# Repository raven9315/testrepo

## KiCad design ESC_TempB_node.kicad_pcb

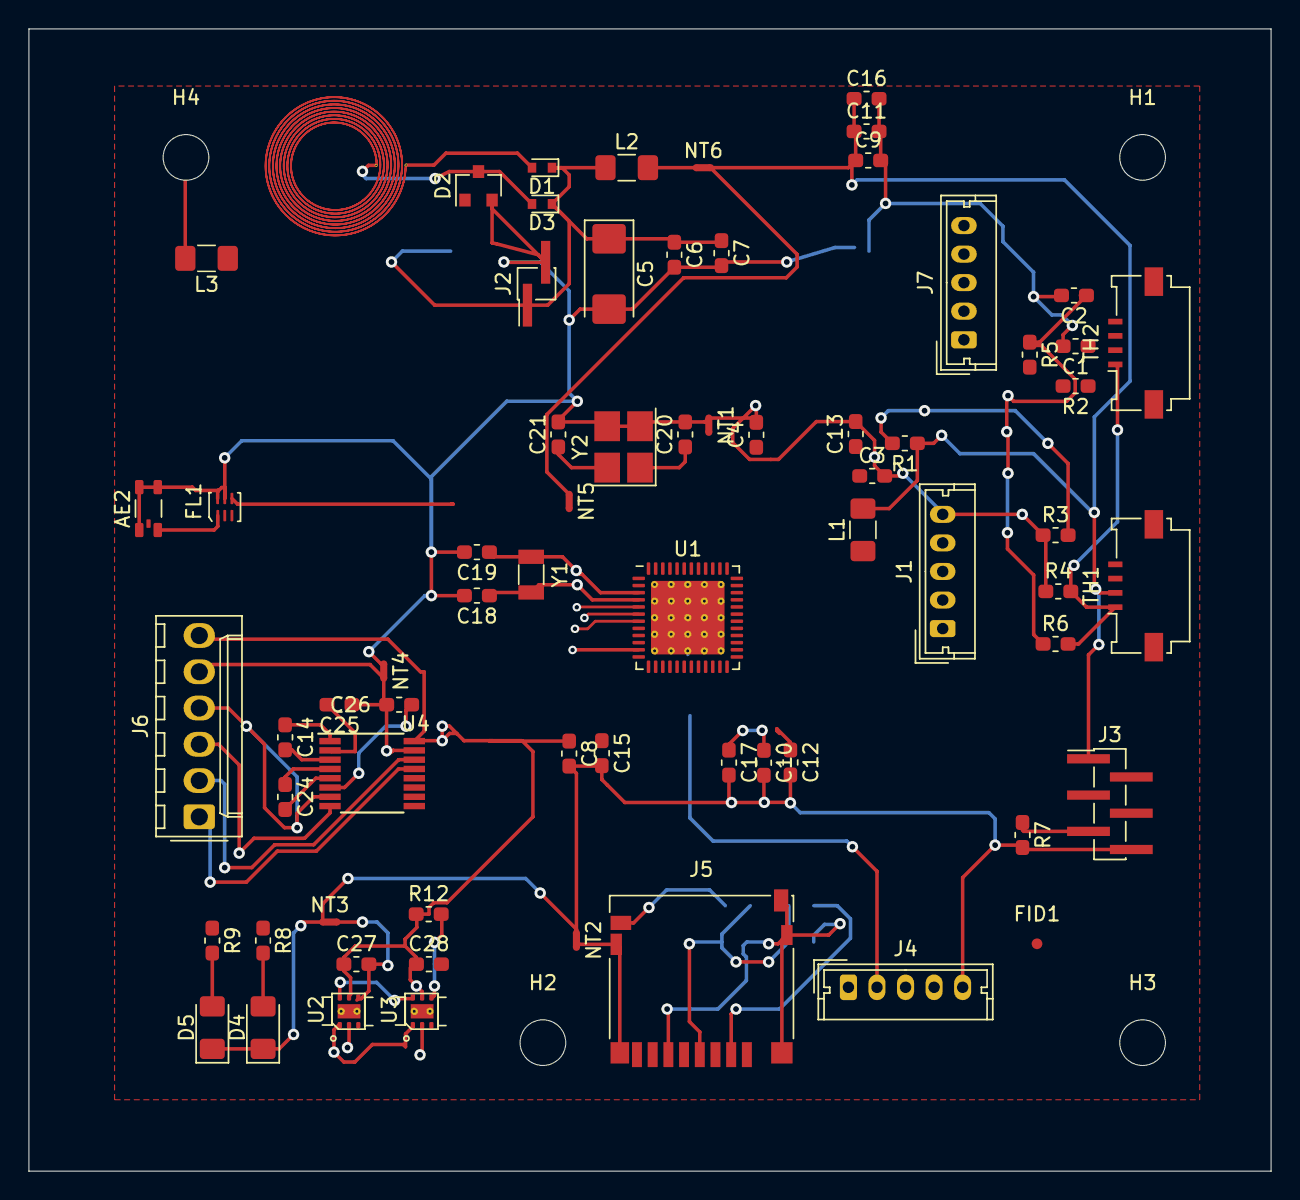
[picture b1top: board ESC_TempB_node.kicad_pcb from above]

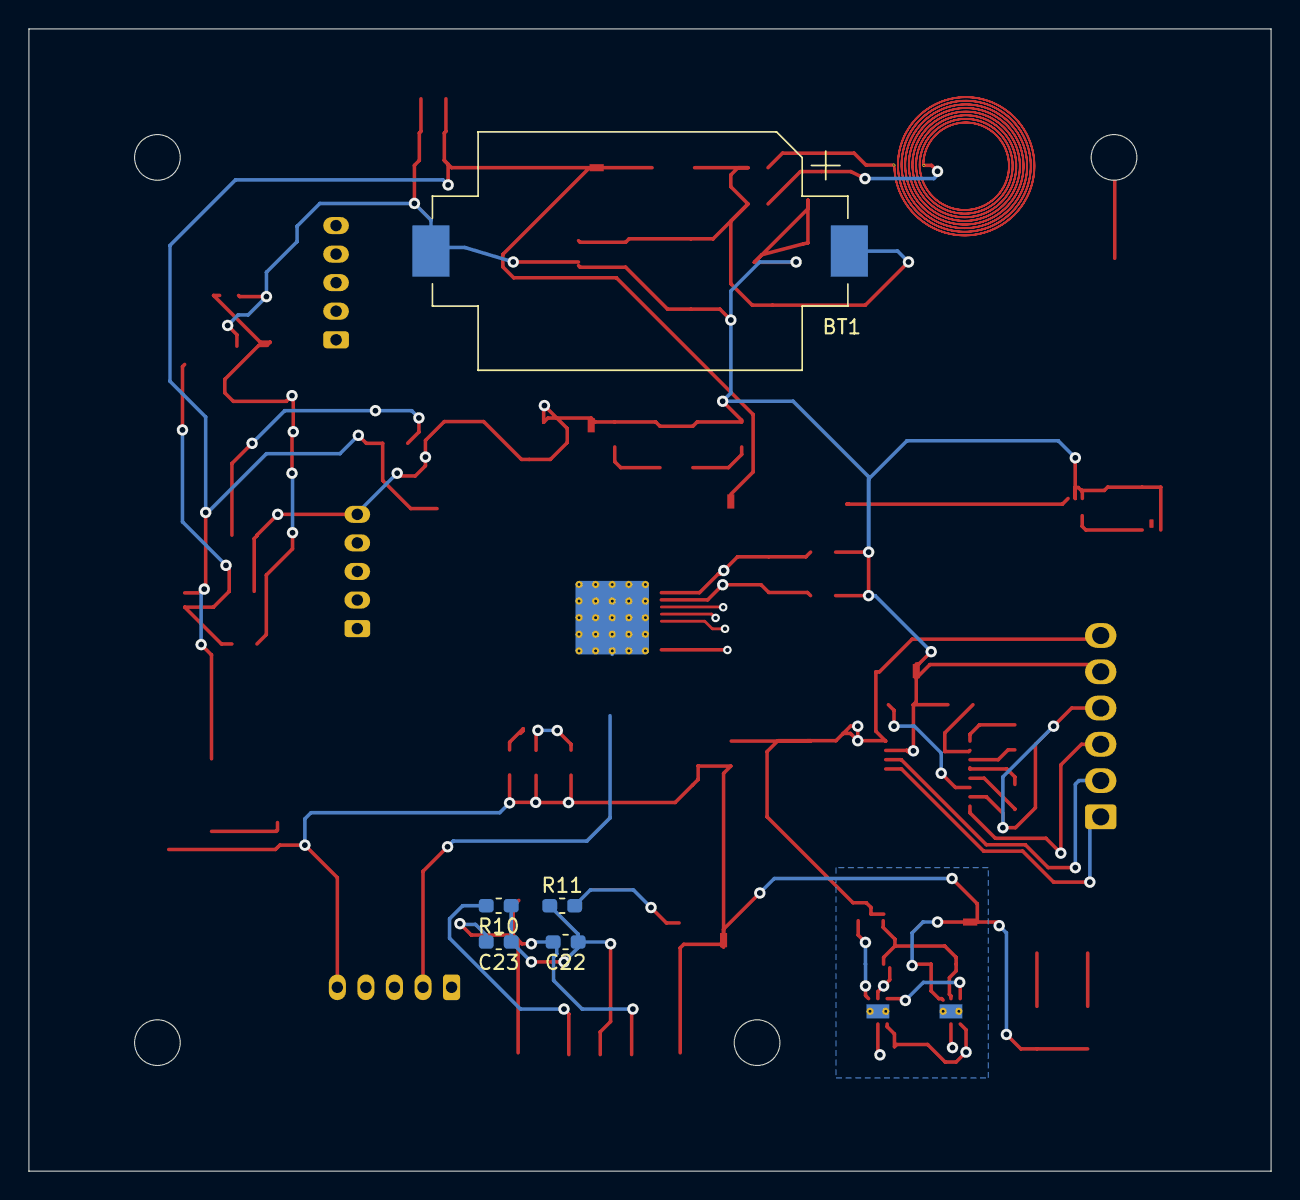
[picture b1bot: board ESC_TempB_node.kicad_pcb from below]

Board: 2 copper layers, 87.0 x 80.0 mm, 78 parts (5 on the bottom side), 71 nets.

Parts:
AE1: Antenna_Loop; Antenna_R10_R13
AE2: Antenna_Chip_4P; JOHANSON_2450AT18D0100
BT1: Battery_2032; BatteryHolder_Keystone_1060_1x2032
C1, C2: 22pF; C_0603_1608Metric_Pad1.05x0.95mm_HandSolder
C3, C4, C6, C11: 10uF; C_0603_1608Metric_Pad1.05x0.95mm_HandSolder
C5: 100uF; CP_EIA-6032-15_Kemet-U
C7, C8, C10, C13, C14, C15, C16, C17, C23, C24, C25, C26, C27, C28: 0.1uF; C_0603_1608Metric_Pad1.05x0.95mm_HandSolder
C9: 2.2uF; C_0603_1608Metric_Pad1.05x0.95mm_HandSolder
C12, C22: 1uF; C_0603_1608Metric_Pad1.05x0.95mm_HandSolder
C18, C19, C20, C21: 12pF; C_0603_1608Metric_Pad1.05x0.95mm_HandSolder
D1, D3: CDBU0130L; D_SOD-523
D2: D_Zener_x2_ACom_AKK; D_SOT-23_NKA
D4: LED GREEN 2012; LED_1206_3216Metric_Pad1.42x1.75mm_HandSolder
D5: LED RED 2012; LED_1206_3216Metric_Pad1.42x1.75mm_HandSolder
FID1: Fiducial; Fiducial_0.75mm_Mask2.25mm
FL1: 2450BM14G0011; JOHANSON-2450BM14G0011
H1, H2, H3, H4: MountingHole_PIN; MountingHole_3.2mm_M3
J1, J4, J7: Conn_01x05_Male; Molex_Micro-Latch_53253-0570_1x05_P2.00mm_Vertical
J2: Conn_01x02_Male; PinHeader_1x02_P1.27mm_Vertical_SMD_Pin1Left
J3: Conn_01x06_Male; PinHeader_1x06_P1.27mm_Vertical_SMD_Pin1Left
J5: Micro_SD_Card_Det; microSD_HC_Hirose_DM3D-SF
J6: Conn_01x06_Female; Molex_KK-254_AE-6410-06A_1x06_P2.54mm_Vertical
L1: 10uH; L_1206_3216Metric_Pad1.42x1.75mm_HandSolder
L2, L3: BLM18HE152SN1; L_1206_3216Metric_Pad1.42x1.75mm_HandSolder
NT1, NT2, NT3, NT4, NT5, NT6: Net-Tie_2; NetTie-2_SMD_Pad0.5mm
R1, R2, R3, R4, R5: 1K; R_0603_1608Metric_Pad1.05x0.95mm_HandSolder
R6: 100K; R_0603_1608Metric_Pad1.05x0.95mm_HandSolder
R7: 10K; R_0603_1608Metric_Pad1.05x0.95mm_HandSolder
R8: 180; R_0603_1608Metric_Pad1.05x0.95mm_HandSolder
R9: 220; R_0603_1608Metric_Pad1.05x0.95mm_HandSolder
R10, R11: 47K; R_0603_1608Metric_Pad1.05x0.95mm_HandSolder
R12: 0R; R_0603_1608Metric_Pad1.05x0.95mm_HandSolder
TH1, TH2: Thermistor_PTC; Molex_200528-0040_1x04-1MP_P1.00mm_Horizontal
U1: CC2640F128RGZR; VQFN-48-1EP_7x7mm_P0.5mm_EP5.15x5.15mm_ThermalVias
U2, U3: TMP117; WSON-6-1EP_2x2mm_P0.65mm_EP1x1.6mm_ThermalVias_tmp117
U4: SP3232EBEY; TSSOP-16_4.4x5mm_P0.65mm
Y1: FC-135 32.7680KA-A3; Crystal_SMD_3215-2Pin_3.2x1.5mm
Y2: TSX-3225 24.0000MF20G-AC3; Crystal_SMD_3225-4Pin_3.2x2.5mm_HandSoldering

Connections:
/ADC0: R1.2, R3.2, U1.36
/ADC1: J7.1, U1.37
/ADC2: R2.2, U1.38
/ADC3: R5.2, U1.39
/ADC4: J7.2, U1.40
/ADC5: J7.3, U1.41
/ADC6: J7.4, U1.42
/ADC7: J7.5, U1.43
/BT_VCC: C4.1, C8.1, C9.1, C10.1, C11.1, C15.1, C16.1, C17.1, C27.1, C28.1, J3.1, J6.6, L1.2, NT5.1, NT6.2, R1.1, R12.1, TH1.2, U1.13, U1.22, U1.45, U2.5, U3.5, U4.16
/CBAT: BT1.1, C5.1, C6.1, C7.1, D1.1, D3.1, J2.1, L2.1
/DCDC_SW: L1.1, U1.33
/DCOUPL: C12.1, U1.23
/DIO_00: U1.5, U4.10
/DIO_01: U1.6, U4.12
/DIO_02_RX: U1.7, U4.9
/DIO_03_TX: U1.8, U4.11
/DIO_04_I2CSCL: U1.9, U2.1, U3.1
/DIO_05_I2CSDA: U1.10, U2.6, U3.6
/DIO_06_LED_RED: R9.1, U1.11
/DIO_07_LED_GR: R8.1, U1.12
/DIO_08_MISO: J5.7, U1.14
/DIO_09_MOSI: J5.3, U1.15
/DIO_10_SPICLK: J5.5, U1.16
/DIO_12_PWM1: J4.1, U1.18
/DIO_13_BTN1: J4.2, U1.19
/DIO_14_BTN2: J4.3, U1.20
/DIO_15: J5.9, R11.2, U1.21
/DIO_18: J1.1, U1.28
/DIO_19: J1.2, U1.29
/DIO_20_FLASH_CS: J5.2, R10.2, U1.30
/DIO_21: J1.3, U1.31
/DIO_22: J1.4, U1.32
/JTAG_TCK: J3.2, U1.25
/JTAG_TDI: J3.3, U1.27
/JTAG_TDO: J3.4, U1.26
/JTAG_TMS: J3.5, R7.1, U1.24
/RESET: C13.1, U1.35
/RF_N: FL1.3, U1.2
/RF_P: FL1.4, U1.1
/RS232/CTS: J6.1, U4.13
/RS232/RTS: J6.4, U4.7
/RS232/RXD: J6.3, U4.8
/RS232/TXD: J6.2, U4.14
/RS_GND: C25.1, C26.1, J6.5, NT4.2, U4.15
/SD_GND: C22.2, C23.2, J5.6, J5.10, J5.11, NT2.2
/SD_VCC: C22.1, C23.1, J5.4, R10.1, R11.1
/SVSS: R4.2, R6.2, TH1.1, TH2.1
/TMP117_GND: C27.2, C28.2, NT3.2, U2.2, U2.4, U3.2
/VBAT: L2.2, NT6.1
/VDDR_RF: C3.1, NT5.2, U1.34, U1.48
/VDDS: NT1.2, U1.44
/X24M_N: C20.1, U1.46, Y2.1
/X24M_P: C21.1, U1.47, Y2.4
/X32K_Q1: C19.1, U1.3, Y1.2
/X32K_Q2: C18.1, U1.4, Y1.1
GND: AE2.2, AE2.3, AE2.4, BT1.2, C1.2, C2.2, C3.2, C4.2, C5.2, C6.2, C7.2, C8.2, C9.2, C10.2, C11.2, C12.2, C13.2, C15.2, C16.2, C17.2, C18.2, C19.2, C20.2, C21.2, D2.1, D4.1, D5.1, FL1.5, FL1.6, J1.5, J2.2, J3.6, J4.5, L3.1, NT1.1, NT2.1, NT3.1, NT4.1, R3.1, R4.1, R7.2, U1.49, Y2.2, Y2.3
unnamed: AE1.1, D2.2, D3.2
unnamed: AE1.2, D1.2
unnamed: AE2.1, FL1.1
unnamed: C1.1, R2.1, TH2.2
unnamed: C2.1, R5.1, R6.1
unnamed: C14.1, U4.1
unnamed: C14.2, U4.3
unnamed: C24.1, U4.4
unnamed: C24.2, U4.5
unnamed: C25.2, U4.2
unnamed: C26.2, U4.6
unnamed: D4.2, R8.2
unnamed: D5.2, R9.2
unnamed: H1.1, H2.1, H3.1, H4.1, L3.2
unnamed: R12.2, U3.4

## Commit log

2021-05-21 first
2021-05-23 add branch v01 add readme .txt
